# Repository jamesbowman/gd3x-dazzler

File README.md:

# gd3x-dazzler

Firmware for the Gameduino 3X Dazzler FPGA

To build:

1. Make sure you are running Python 3 in a virtual environment. The build is tested with 3.7 onwards

2. Install the tools:
   sudo apt-get -y install verilator gforth

3. Install the Python requirements:
   pip install -r requirements.txt

Then edit `xilinxmake` to point to your Xilinx WebPack installation.

After this `make` will build the firmware.

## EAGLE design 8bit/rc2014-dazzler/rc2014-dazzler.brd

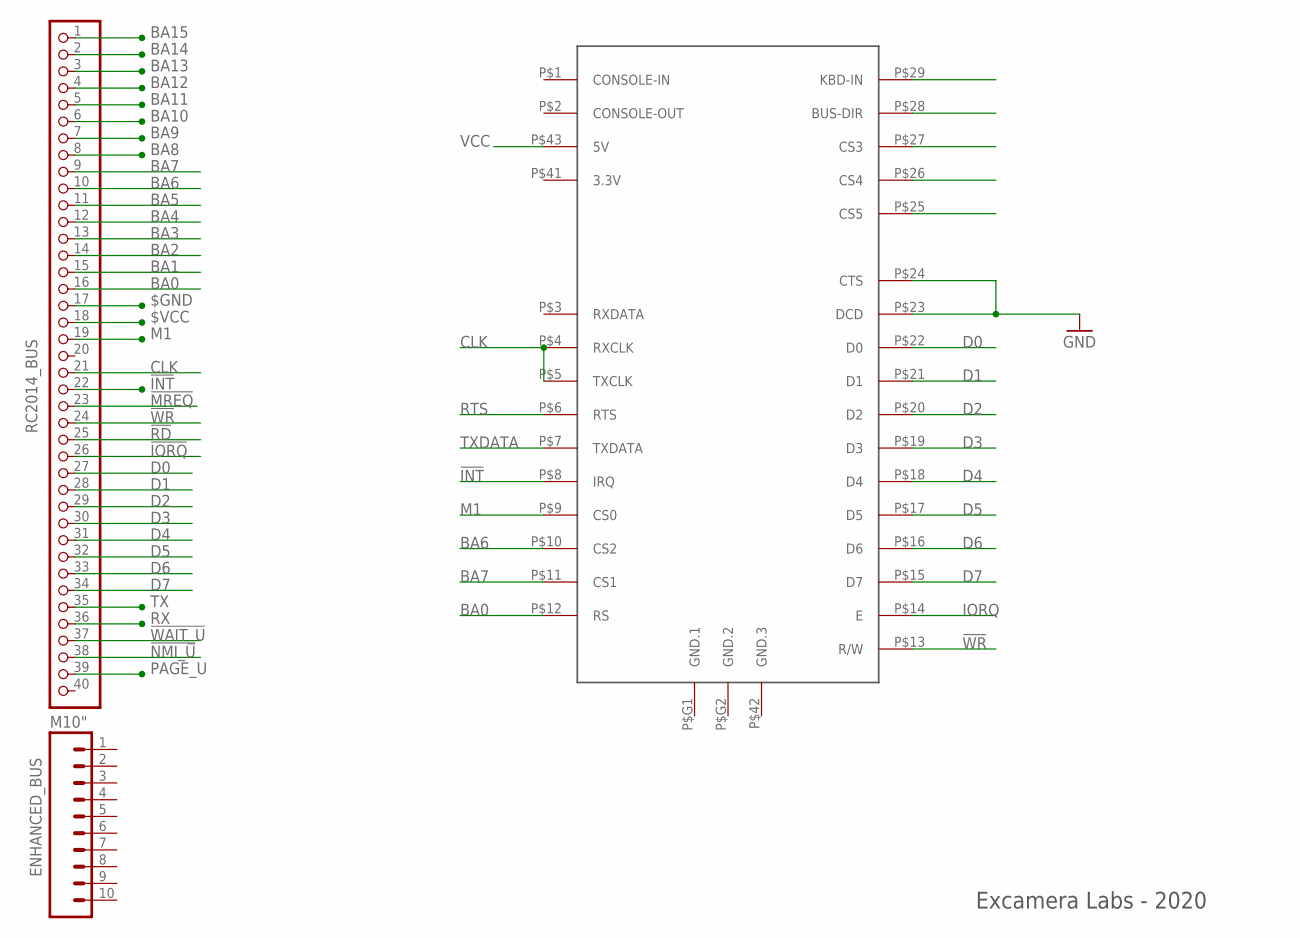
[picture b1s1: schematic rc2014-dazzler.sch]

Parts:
ENHANCED_BUS: M10"; 1X10
RC2014_BUS: RC2014 BUS; 1X40
U$1: DAZZLER-6850-SOCKET; DAZZLER-SOCKET

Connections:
!INT: RC2014_BUS.22, U$1.P$8 (IRQ)
!IORQ: RC2014_BUS.26
!MREQ: RC2014_BUS.23
!NMI_U: RC2014_BUS.38
!RD: RC2014_BUS.25
!WAIT_U: RC2014_BUS.37
!WR: RC2014_BUS.24, U$1.P$13 (R/W)
$GND: RC2014_BUS.17
$VCC: RC2014_BUS.18
BA0: RC2014_BUS.16, U$1.P$12 (RS)
BA1: RC2014_BUS.15
BA2: RC2014_BUS.14
BA3: RC2014_BUS.13
BA4: RC2014_BUS.12
BA5: RC2014_BUS.11
BA6: RC2014_BUS.10, U$1.P$10 (CS2)
BA7: RC2014_BUS.9, U$1.P$11 (CS1)
BA8: RC2014_BUS.8
BA9: RC2014_BUS.7
BA10: RC2014_BUS.6
BA11: RC2014_BUS.5
BA12: RC2014_BUS.4
BA13: RC2014_BUS.3
BA14: RC2014_BUS.2
BA15: RC2014_BUS.1
CLK: RC2014_BUS.21, U$1.P$4 (RXCLK), U$1.P$5 (TXCLK)
D0: RC2014_BUS.27, U$1.P$22 (D0)
D1: RC2014_BUS.28, U$1.P$21 (D1)
D2: RC2014_BUS.29, U$1.P$20 (D2)
D3: RC2014_BUS.30, U$1.P$19 (D3)
D4: RC2014_BUS.31, U$1.P$18 (D4)
D5: RC2014_BUS.32, U$1.P$17 (D5)
D6: RC2014_BUS.33, U$1.P$16 (D6)
D7: RC2014_BUS.34, U$1.P$15 (D7)
GND: U$1.P$23 (DCD), U$1.P$24 (CTS)
IORQ: U$1.P$14 (E)
M1: RC2014_BUS.19, U$1.P$9 (CS0)
PAGE_U: RC2014_BUS.39
RTS: U$1.P$6 (RTS)
RX: RC2014_BUS.36
TX: RC2014_BUS.35
TXDATA: U$1.P$7 (TXDATA)
VCC: U$1.P$43 (5V)

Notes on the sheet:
Excamera Labs - 2020

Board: 4 copper layers, 3 parts (0 on the bottom side), 16 nets, no tracks yet.

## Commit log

2020-05-28 Initial import
2020-05-28 Travis attempt
2020-05-28 Travis add gforth
2020-05-28 Make empty build dir
2020-05-28 Tabs
2020-05-28 Verilator 3.884 broke backwards compatibility with l2-name.
    Many distros still ship with Verilator 3.856
    This is the best band-aid I can come up with to fix the mess.
2020-05-28 Any verilator version before 3.884
2020-07-05 Checkpoint, 0.0.1 UCF
2020-07-05 Retain 0.1.0 board UCF
2020-07-05 PCB 1.0.0 UCF
2020-07-05 Rename 0.1.0 signals to final 1.0.0 names
2020-07-06 QSPI for BT815 interface, first cut
2020-07-06 Quad SPI to EVE
2020-07-06 EVE quad test
2020-07-07 Clean up SPI ports
2020-07-07 Confirm SPI flash in quad mode
2020-07-10 Test synthesis for PCB 1.1.0
2020-07-11 Clean up SPI interface code
2020-07-12 Clean up j1/Makefile, and build dazzler.hex
2020-07-12 switch to a more efficient J1-specific DEFER impl
2020-07-12 complete QPI stack
2020-07-12 More work-around code for Verilator's breaking change at 3.888
2020-07-17 Badge for Travis build
2020-07-20 HDMI rework, confirmed with tv.py. Data islands are all zero.
2020-07-20 Avoid importing "tv"
2020-07-20 Data island now carrying TERC4
2020-07-20 Fix 2.7 style library names in Makefile.
2020-07-21 ECC codes
2020-07-21 45 line cycle for ID packets
2020-07-22 Simplify horizontal sequencer
2020-07-22 use 3 data island slots per line
2020-07-23 Proper audio sequencer
2020-07-24 Refactor, ready for sample FIFO
2020-07-25 Audio interface
2020-07-25 Audio mock source at 48 kHz
2020-07-25 Use new clean HDMI interface
2020-07-26 Use felix image to confirm video out
2020-07-26 Valid audio output, sync integrator to 48 kHz tick
2020-07-26 Frequency is now an input
2020-07-26 flash loader works in qpi mode
2020-07-26 New command #binclude for binary include
2020-08-10 DNA string on boot
2020-08-11 video bus debug, DNA port, i2c test
2020-08-28 sd card bringup
2020-08-30 FAT32 ls and cat
2020-08-30 Add proper cluster handling to sd
2020-08-31 Filesystem, loading done
2020-09-08 Proper SD SPI support
2020-09-10 build versioning, multiboot support
2020-09-11 New word loadsd
2020-09-11 Set conflig clk to maximum of 26 MHz for faster boot
2020-09-11 Stamp generator
2020-09-12 Data out from ICAP, first working
2020-09-12 icap register reads working
2020-09-14 Proper boot sequence
2020-10-11 Eagle library parts
2020-10-15 Asteroids integrated
2020-10-15 New requirements for Python
2020-10-25 Textmode Python reference, import
2020-10-25 textmode first test
2020-10-25 passlist
2020-10-25 First SGR
2020-10-25 test cases
2020-10-26 256 color support
2020-10-26 Clean up
2020-10-26 C implemented
2020-10-26 CSI A
2020-10-26 H handled
2020-10-26 More passes
2020-10-26 Full passlist
2020-10-26 Refactor clears
2020-10-26 New tests
2020-10-27 Small optimizations
2020-10-27 Checkpoint
2020-10-27 Clean up arg
2020-10-28 New passes
2020-11-08 more test cases. pygments and long line test
2020-11-08 More tests passing
2020-11-09 Hello world
2020-11-26 Bringup, asteroids, textmode split
2020-11-26 Scrolling
2020-11-26 More consolidation
2020-11-27 Add c! instruction
2020-11-27 miniloader added to nuc.fs
2020-11-27 Dump all 16K
2020-11-28 Multiboot images ready
2020-11-28 image builder
2020-11-28 Fix J1 PC[12] alu bug
2020-11-28 wii cleanup, wiisense array
2020-11-28 slot loaders
2020-11-28 wii polling, overflow guard in DVG emulator
2020-11-28 Stream loading using slot offsets
2020-11-29 New slot loaders
2020-11-29 textmode refactoring
2020-11-29 Split out portable component
2020-11-29 textmode first character
2020-11-29 slot words
2020-11-29 Confirm 16-bit clean
2020-11-29 test case runner
2020-11-30 textmode running
2020-11-30 Cleaner boot image building Boot menu selection functional
2020-11-30 Base bootfile
2020-12-01 menu control moved to wii
2020-12-01 Eagle board proto
2020-12-04 SPI command mailbox
2020-12-04 slot 1 alternate
2020-12-06 Text mode blinking cursor
2020-12-06 First firmware builder
2020-12-06 Generate textmode init from actual model
2020-12-06 Remove old headers
2020-12-06 Split _bringup.fs and _flash.fs into first pass
2020-12-07 Multiple screen modes
2020-12-07 Clean up firmware builder
2020-12-07 Top-level Makefile
2020-12-07 bootmenu from microSD
2020-12-07 firmware build
2020-12-07 Add firmware assets
2020-12-07 P15 is microSD detect, add a pullup
2020-12-08 Special general5 0xda22 only for manufacturing image
2020-12-08 Clean up da22 code image
2020-12-08 Avoid eve reset after loading flash
2020-12-08 Info banner over console on startup
2020-12-09 Fix missing build/ for stamp.fs
2020-12-09 Build order fix
2020-12-09 Font path
2020-12-09 fix font path for image builder
2020-12-09 Text mode does not need spidriver to build
2021-01-11 Dazzler library part for Eagle
2021-01-11 Version 1.1.0
2021-01-11 bteve as a requirement
2021-01-11 fonts for build
2021-01-28 Commit missing script
    [#1]
2021-01-28 GPIO mode, disabled
2021-01-28 Add .fonts dir
2021-01-28 Forth checkpoint for 1.1.0
2021-01-28 Fix signal duplication bug on Verilator
2021-01-28 Missing source
2021-01-28 Make Asteroids optional
2021-01-28 Remove old header dependencies
2021-01-28 Add missing production UCF
2021-01-28 Include font for main logo
2021-01-28 Fix memory interface registers
2021-01-28 Remove icestorm reference
2021-01-29 Add build instructions [#1]
2021-02-03 Update VertexTranslateY calls to use pixels, not 1/16th pixels
    Tracking change in py-bteve
    [#2]
2021-02-03 Command line flag for visualization mode
2021-02-03 Better wording
2021-02-03 Fix boot menu PointSize and LineSize to be in pixels
    tracking bteve API change.
    [#3]
2021-07-24 Typo

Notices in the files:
parts and their libraries:
SparkFun: Licensing: CC v3.0 Share-Alike You are welcome to use this library for commercial purposes.
